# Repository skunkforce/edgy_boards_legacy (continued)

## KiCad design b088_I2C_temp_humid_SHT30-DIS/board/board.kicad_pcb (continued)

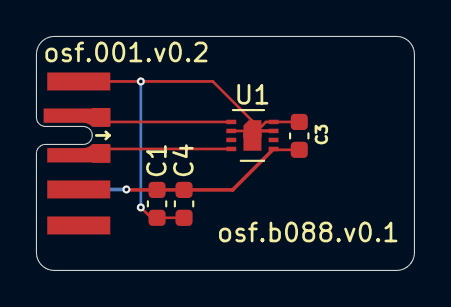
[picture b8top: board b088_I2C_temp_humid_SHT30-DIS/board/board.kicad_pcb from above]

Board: 2 copper layers, 21.0 x 13.0 mm, 5 parts (0 on the bottom side), 4 nets.
